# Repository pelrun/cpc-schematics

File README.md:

## Amstrad CPC6128 version 2 (MC0020x) schematic and pcb.

This is intended to be a reasonably accurate KiCad 6 transcription of the version 2 6128 pcb, with the 40010 Gate Array and the 24-pin disk data separator. The Amstrad service manuals don't bother to document this version, instead providing a mishmash of earlier and later revision schematics and pcb track layouts.

There are some liberties taken due to practical difficulties in reading the top layer of the PCB, so here's the priorities of this version:

- Schematic should match as closely as possible to the real board.
- All parts and part references and logical connectivity should match exactly.
- Part and via placement should match as closely as possible.
- Track routing should match closely on both sides of the pcb; all vias should be connected to the correct nets.
- Exact track poses may vary; original layout was done by hand and has varying angles; kicad layout is kept at 45 degrees.
- Track widths aren't correct everywhere; while the ground and power nets are handled by a netclass, a bunch of the tracks in the audio circuit need to have their widths manually adjusted.

Most part values should be correct, but I've not yet bothered to check any resistors - all values were copied from corresponding parts identified in the official schematics for the other revisions. Real values may be different, and additional resistors that are present but not documented elsewhere have been left with a value of "?".

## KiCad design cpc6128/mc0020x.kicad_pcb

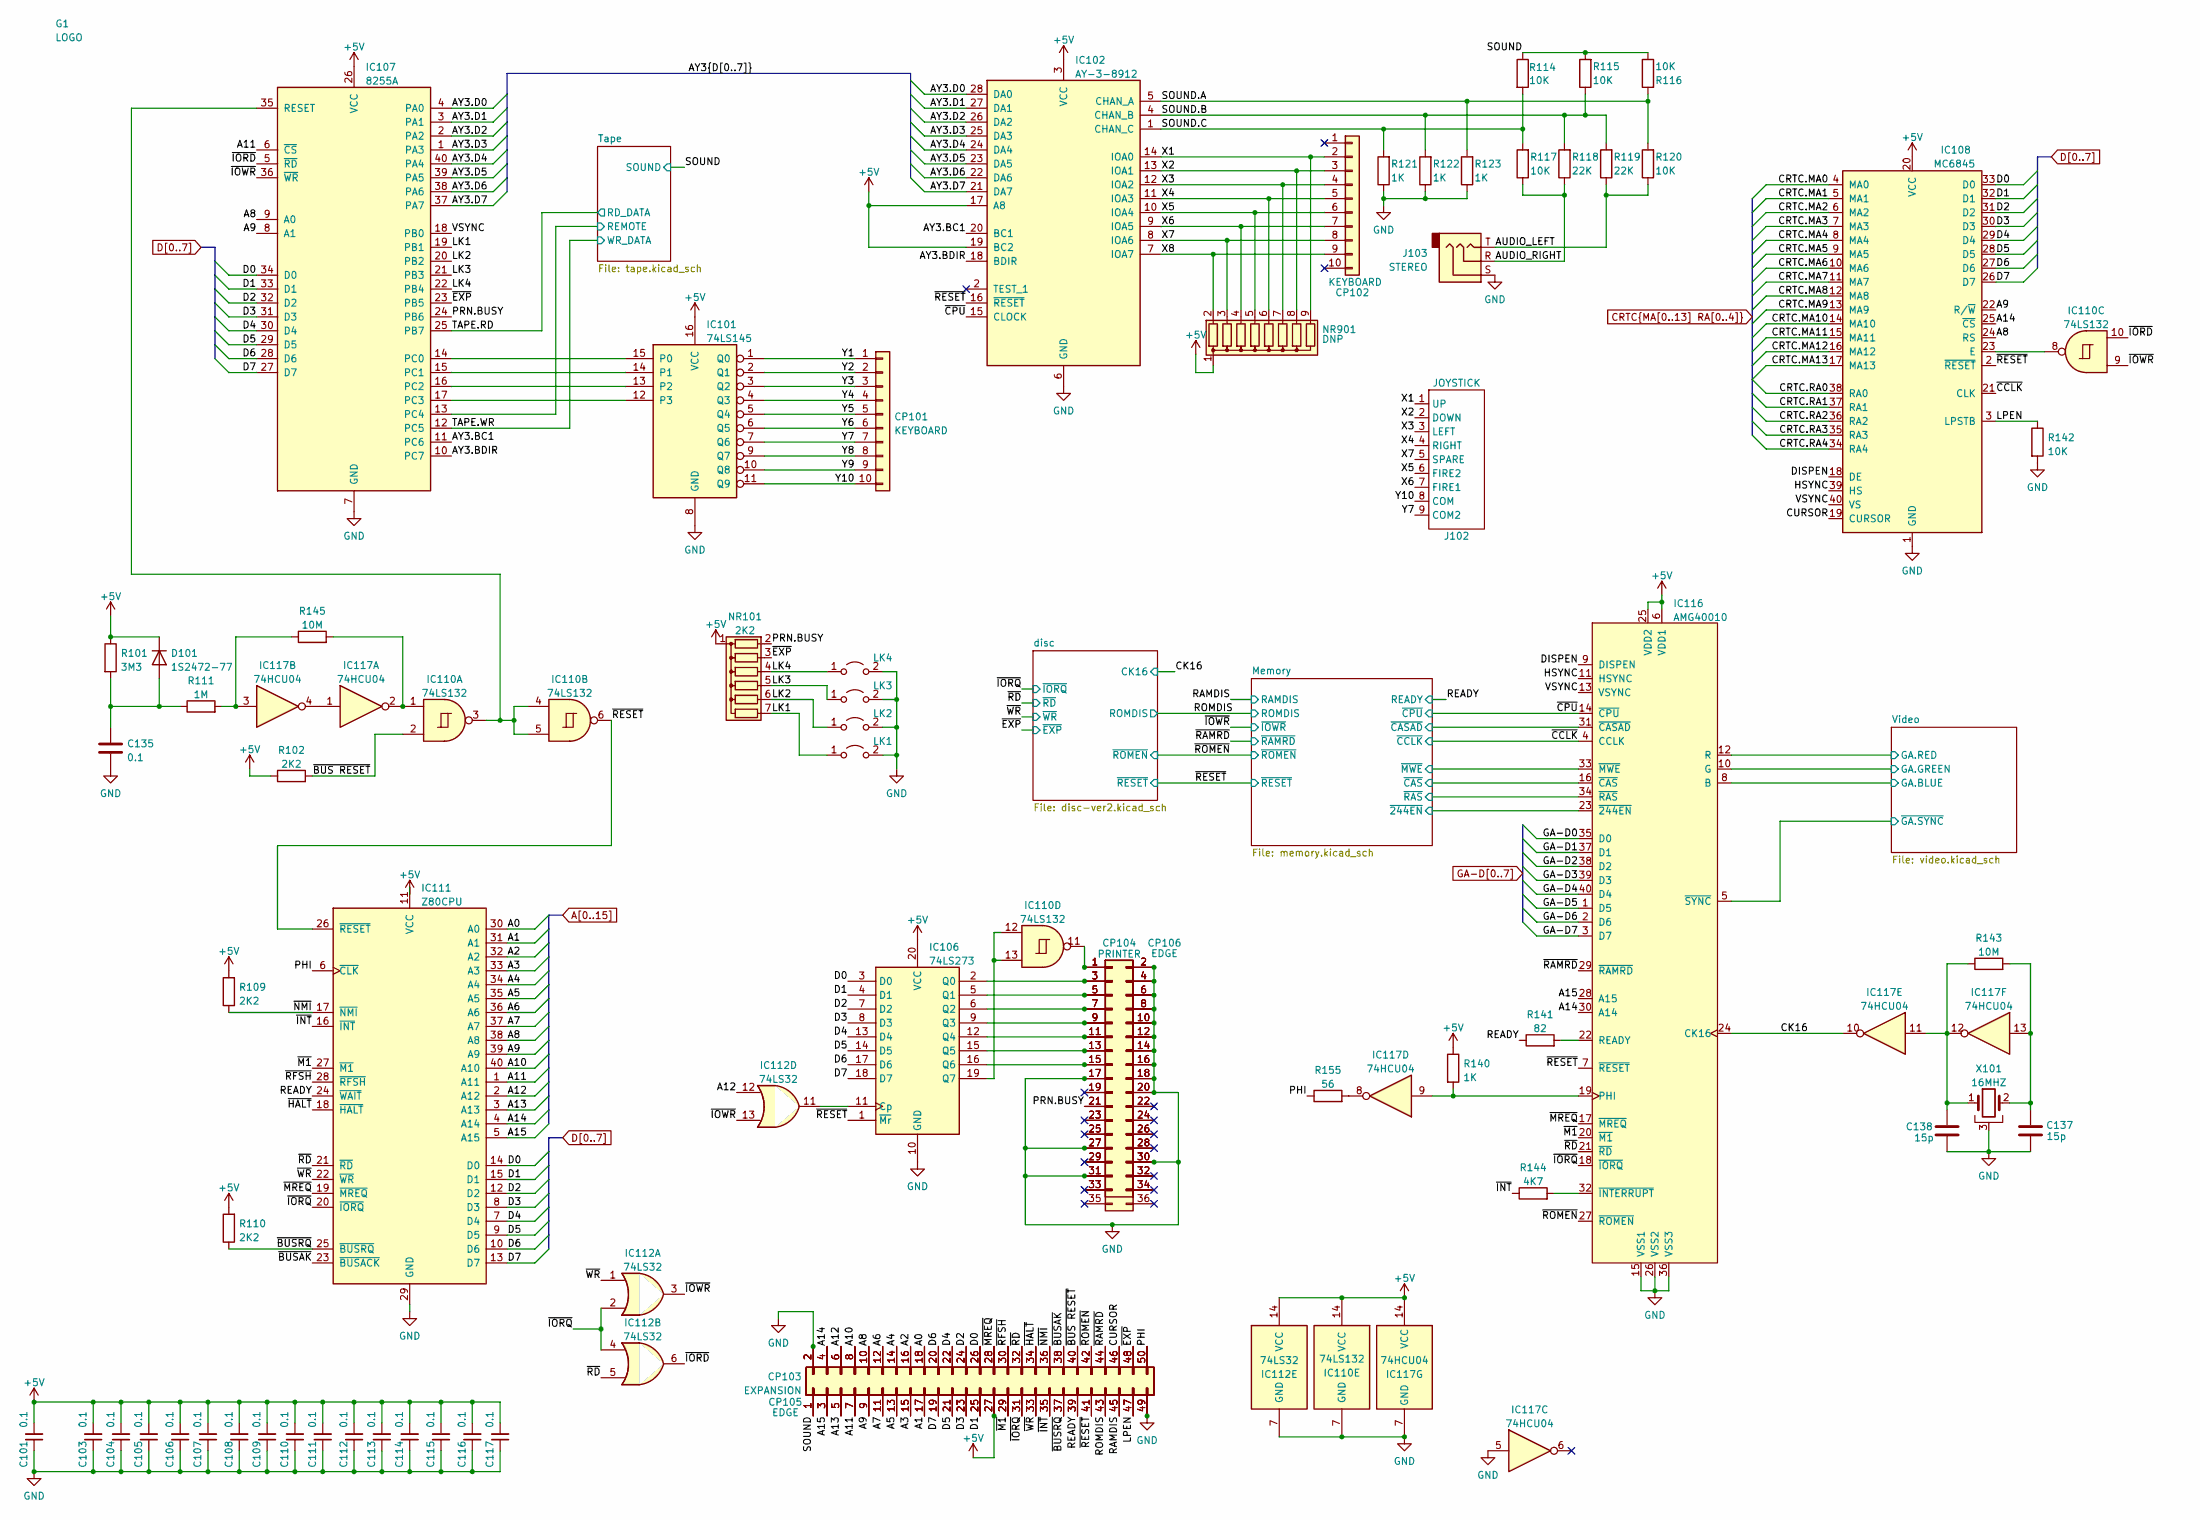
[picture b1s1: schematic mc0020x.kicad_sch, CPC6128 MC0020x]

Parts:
C101, C103, C104, C105, C106, C107, C108, C109, C110, C111, C112, C113, C114, C115, C116, C117, C135: 0.1; C_Disc_D4.3mm_W1.9mm_P5.00mm
C137, C138: 15p; C_Disc_D4.3mm_W1.9mm_P5.00mm
CP101, CP102: KEYBOARD; HBLB10S-5J
CP103: EXPANSION; 50-PIN-CENTRONICS
CP104: PRINTER; 36-PIN-CENTRONICS
CP105: EDGE; Edge_Conn_2x25
CP106: EDGE; Edge_Conn_2x17
D101: 1S2472-77; D_DO-35_SOD27_P10.16mm_Horizontal
G1: LOGO
IC101: 74LS145; DIP-16_W7.62mm
IC102: AY-3-8912; DIP-28_W15.24mm
IC106: 74LS273; DIP-20_W7.62mm
IC107: 8255A; DIP-40_W15.24mm
IC108: MC6845; DIP-40_W15.24mm
IC110: 74LS132; DIP-14_W7.62mm
IC111: Z80CPU; DIP-40_W15.24mm
IC112: 74LS32; DIP-14_W7.62mm
IC116: AMG40010; DIP-40_W15.24mm_Socket
IC117: 74HCU04; DIP-14_W7.62mm
J102: JOYSTICK; DSUB-9_Male_Horizontal_P2.77x2.54mm_EdgePinOffset9.40mm
J103: STEREO; HSJ1061-0104409
LK1, LK2, LK3, LK4: Jumper_2_Open; LINK
NR101: 2K2; R_Array_SIP7
NR901: DNP; R_Array_SIP9
R101: 3M3; R_Axial_DIN0207_L6.3mm_D2.5mm_P10.16mm_Horizontal
R102, R109, R110: 2K2; R_Axial_DIN0207_L6.3mm_D2.5mm_P10.16mm_Horizontal
R111: 1M; R_Axial_DIN0207_L6.3mm_D2.5mm_P10.16mm_Horizontal
R114, R115, R116, R117, R120, R142: 10K; R_Axial_DIN0207_L6.3mm_D2.5mm_P10.16mm_Horizontal
R118, R119: 22K; R_Axial_DIN0207_L6.3mm_D2.5mm_P10.16mm_Horizontal
R121, R122, R123, R140: 1K; R_Axial_DIN0207_L6.3mm_D2.5mm_P10.16mm_Horizontal
R141: 82; R_Axial_DIN0207_L6.3mm_D2.5mm_P10.16mm_Horizontal
R143, R145: 10M; R_Axial_DIN0207_L6.3mm_D2.5mm_P10.16mm_Horizontal
R144: 4K7; R_Axial_DIN0207_L6.3mm_D2.5mm_P10.16mm_Horizontal
R155: 56; R_Axial_DIN0207_L6.3mm_D2.5mm_P10.16mm_Horizontal
X101: 16MHZ; Crystal_HC18-U_Horizontal_1EP_style1

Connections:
+5V: C101.2, C103.2, C104.2, C105.2, C106.2, C107.2, C108.2, C109.2, C110.2, C111.2, C112.2, C113.2, C114.2, C115.2, C116.2, C117.2, CP103.27, CP105.27, D101.1 (K), IC101.16 (VCC), IC102.3 (VCC), IC102.17 (A8), IC102.19 (BC2), IC106.20 (VCC), IC107.26 (VCC), IC108.20 (VCC), IC110.14 (VCC), IC111.11 (VCC), IC112.14 (VCC), IC116.6 (VDD1), IC116.25 (VDD2), IC117.14 (VCC), NR101.1 (common), NR901.1 (common), R101.1, R102.1, R109.2, R110.2, R140.1; also elsewhere on the board
/AUDIO_LEFT: J103.T, R119.1, R120.1
/AUDIO_RIGHT: J103.R, R117.1, R118.1
/AY3.BC1: IC102.20 (BC1), IC107.11 (PC6)
/AY3.BDIR: IC102.18 (BDIR), IC107.10 (PC7)
/AY3.D0: IC102.28 (DA0), IC107.4 (PA0)
/AY3.D1: IC102.27 (DA1), IC107.3 (PA1)
/AY3.D2: IC102.26 (DA2), IC107.2 (PA2)
/AY3.D3: IC102.25 (DA3), IC107.1 (PA3)
/AY3.D4: IC102.24 (DA4), IC107.40 (PA4)
/AY3.D5: IC102.23 (DA5), IC107.39 (PA5)
/AY3.D6: IC102.22 (DA6), IC107.38 (PA6)
/AY3.D7: IC102.21 (DA7), IC107.37 (PA7)
/CK16: IC116.24 (CK16), IC117.10; also elsewhere on the board
/CURSOR: CP103.46, CP105.46, IC108.19 (CURSOR)
/DISPEN: IC108.18 (DE), IC116.9 (DISPEN)
/HSYNC: IC108.39 (HS), IC116.11 (HSYNC)
/LK1: IC107.19 (PB1), LK1.1 (A), NR101.7 (R6)
/LK2: IC107.20 (PB2), LK2.1 (A), NR101.6 (R5)
/LK3: IC107.21 (PB3), LK3.1 (A), NR101.5 (R4)
/LK4: IC107.22 (PB4), LK4.1 (A), NR101.4 (R3)
/LPEN: CP103.47, CP105.47, IC108.3 (LPSTB), R142.1
/Memory/~244EN: IC116.23 (~244EN); also elsewhere on the board
/Memory/~CASAD: IC116.31 (~CASAD); also elsewhere on the board
/Memory/~CAS: IC116.16 (~CAS); also elsewhere on the board
/Memory/~MWE: IC116.33 (~MWE); also elsewhere on the board
/Memory/~RAS: IC116.34 (~RAS); also elsewhere on the board
/PHI: CP103.50, CP105.50, IC111.6 (~CLK), R155.1
/PRN.BUSY: CP104.21, CP106.21, IC107.24 (PB6), NR101.2 (R1)
/RAMDIS: CP103.45, CP105.45; also elsewhere on the board
/READY: CP103.39, CP105.39, IC111.24 (~WAIT), R141.1; also elsewhere on the board
/ROMDIS: CP103.43, CP105.43; also elsewhere on the board
/SOUND: CP103.1, CP105.1, R114.1, R115.2, R116.1; also elsewhere on the board
/SOUND.A: IC102.5 (CHAN_A), R116.2, R120.2, R123.2
/SOUND.B: IC102.4 (CHAN_B), R115.1, R118.2, R119.2, R122.2
/SOUND.C: IC102.1 (CHAN_C), R114.2, R117.2, R121.2
/TAPE.RD: IC107.25 (PB7); also elsewhere on the board
/TAPE.WR: IC107.12 (PC5); also elsewhere on the board
/Tape/REMOTE: IC107.13 (PC4); also elsewhere on the board
/VSYNC: IC107.18 (PB0), IC108.40 (VS), IC116.13 (VSYNC)
/Video/GA.BLUE: IC116.8 (B); also elsewhere on the board
/Video/GA.GREEN: IC116.10 (G); also elsewhere on the board
/Video/GA.RED: IC116.12 (R); also elsewhere on the board
/Video/~GA.SYNC: IC116.5 (~SYNC); also elsewhere on the board
/X1: CP102.2, IC102.14 (IOA0), J102.1 (UP), NR901.9 (R8)
/X2: CP102.3, IC102.13 (IOA1), J102.2 (DOWN), NR901.8 (R7)
/X3: CP102.4, IC102.12 (IOA2), J102.3 (LEFT), NR901.7 (R6)
/X4: CP102.5, IC102.11 (IOA3), J102.4 (RIGHT), NR901.6 (R5)
/X5: CP102.6, IC102.10 (IOA4), J102.6 (FIRE2), NR901.5 (R4)
/X6: CP102.7, IC102.9 (IOA5), J102.7 (FIRE1), NR901.4 (R3)
/X7: CP102.8, IC102.8 (IOA6), J102.5 (SPARE), NR901.3 (R2)
/X8: CP102.9, IC102.7 (IOA7), NR901.2 (R1)
/Y1: CP101.1, IC101.1 (Q0)
/Y2: CP101.2, IC101.2 (Q1)
/Y3: CP101.3, IC101.3 (Q2)
/Y4: CP101.4, IC101.4 (Q3)
/Y5: CP101.5, IC101.5 (Q4)
/Y6: CP101.6, IC101.6 (Q5)
/Y7: CP101.7, IC101.7 (Q6), J102.9 (COM2)
/Y8: CP101.8, IC101.9 (Q7)
/Y9: CP101.9, IC101.10 (Q8)
/Y10: CP101.10, IC101.11 (Q9), J102.8 (COM)
/~BUS RESET: CP103.40, CP105.40, IC110.2, R102.2
/~BUSAK: CP103.38, CP105.38, IC111.23 (~BUSACK)
/~BUSRQ: CP103.37, CP105.37, IC111.25 (~BUSRQ), R110.1
/~CCLK: IC108.21 (CLK), IC116.4 (CCLK); also elsewhere on the board
/~CPU: IC102.15 (CLOCK), IC116.14 (~CPU); also elsewhere on the board
/~EXP: CP103.48, CP105.48, IC107.23 (PB5), NR101.3 (R2); also elsewhere on the board
/~HALT: CP103.34, CP105.34, IC111.18 (~HALT)
/~INT: CP103.35, CP105.35, IC111.16 (~INT), R144.1
/~IORD: IC107.5 (~RD), IC110.10, IC112.6
/~IORQ: CP103.31, CP105.31, IC111.20 (~IORQ), IC112.2, IC112.4, IC116.18 (~IORQ); also elsewhere on the board
/~IOWR: IC107.36 (~WR), IC110.9, IC112.3, IC112.13; also elsewhere on the board
/~M1: CP103.29, CP105.29, IC111.27 (~M1), IC116.20 (~M1)
/~MREQ: CP103.28, CP105.28, IC111.19 (~MREQ), IC116.17 (~MREQ)
/~NMI: CP103.36, CP105.36, IC111.17 (~NMI), R109.1
/~RAMRD: CP103.44, CP105.44, IC116.29 (~RAMRD); also elsewhere on the board
/~RD: CP103.32, CP105.32, IC111.21 (~RD), IC112.5, IC116.21 (~RD); also elsewhere on the board
/~RESET: CP103.41, CP105.41, IC102.16 (~RESET), IC106.1 (~Mr), IC108.2 (~RESET), IC110.6, IC111.26 (~RESET), IC116.7 (~RESET); also elsewhere on the board
/~RFSH: CP103.30, CP105.30, IC111.28 (~RFSH)
/~ROMEN: CP103.42, CP105.42, IC116.27 (~ROMEN); also elsewhere on the board
/~WR: CP103.33, CP105.33, IC111.22 (~WR), IC112.1; also elsewhere on the board
A0: CP103.18, CP105.18, IC111.30 (A0); also elsewhere on the board
A1: CP103.17, CP105.17, IC111.31 (A1); also elsewhere on the board
A2: CP103.16, CP105.16, IC111.32 (A2); also elsewhere on the board
A3: CP103.15, CP105.15, IC111.33 (A3); also elsewhere on the board
A4: CP103.14, CP105.14, IC111.34 (A4); also elsewhere on the board
A5: CP103.13, CP105.13, IC111.35 (A5); also elsewhere on the board
A6: CP103.12, CP105.12, IC111.36 (A6); also elsewhere on the board
A7: CP103.11, CP105.11, IC111.37 (A7); also elsewhere on the board
A8: CP103.10, CP105.10, IC107.9 (A0), IC108.24 (RS), IC111.38 (A8); also elsewhere on the board
A9: CP103.9, CP105.9, IC107.8 (A1), IC108.22 (R/~W), IC111.39 (A9); also elsewhere on the board
A10: CP103.8, CP105.8, IC111.40 (A10); also elsewhere on the board
A11: CP103.7, CP105.7, IC107.6 (~CS), IC111.1 (A11); also elsewhere on the board
A12: CP103.6, CP105.6, IC111.2 (A12), IC112.12; also elsewhere on the board
A13: CP103.5, CP105.5, IC111.3 (A13); also elsewhere on the board
A14: CP103.4, CP105.4, IC108.25 (~CS), IC111.4 (A14), IC116.30 (A14); also elsewhere on the board
A15: CP103.3, CP105.3, IC111.5 (A15), IC116.28 (A15); also elsewhere on the board
CRTC.MA0: IC108.4 (MA0); also elsewhere on the board
CRTC.MA1: IC108.5 (MA1); also elsewhere on the board
CRTC.MA2: IC108.6 (MA2); also elsewhere on the board
CRTC.MA3: IC108.7 (MA3); also elsewhere on the board
CRTC.MA4: IC108.8 (MA4); also elsewhere on the board
CRTC.MA5: IC108.9 (MA5); also elsewhere on the board
CRTC.MA6: IC108.10 (MA6); also elsewhere on the board
CRTC.MA7: IC108.11 (MA7); also elsewhere on the board
CRTC.MA8: IC108.12 (MA8); also elsewhere on the board
CRTC.MA9: IC108.13 (MA9); also elsewhere on the board
CRTC.MA10: IC108.14 (MA10)
CRTC.MA11: IC108.15 (MA11)
CRTC.MA12: IC108.16 (MA12); also elsewhere on the board
CRTC.MA13: IC108.17 (MA13); also elsewhere on the board
CRTC.RA0: IC108.38 (RA0); also elsewhere on the board
CRTC.RA1: IC108.37 (RA1); also elsewhere on the board
CRTC.RA2: IC108.36 (RA2); also elsewhere on the board
CRTC.RA3: IC108.35 (RA3)
CRTC.RA4: IC108.34 (RA4)
D0: CP103.26, CP105.26, IC106.3 (D0), IC107.34 (D0), IC108.33 (D0), IC111.14 (D0); also elsewhere on the board
D1: CP103.25, CP105.25, IC106.4 (D1), IC107.33 (D1), IC108.32 (D1), IC111.15 (D1); also elsewhere on the board
D2: CP103.24, CP105.24, IC106.7 (D2), IC107.32 (D2), IC108.31 (D2), IC111.12 (D2); also elsewhere on the board
D3: CP103.23, CP105.23, IC106.8 (D3), IC107.31 (D3), IC108.30 (D3), IC111.8 (D3); also elsewhere on the board
D4: CP103.22, CP105.22, IC106.13 (D4), IC107.30 (D4), IC108.29 (D4), IC111.7 (D4); also elsewhere on the board
D5: CP103.21, CP105.21, IC106.14 (D5), IC107.29 (D5), IC108.28 (D5), IC111.9 (D5); also elsewhere on the board
D6: CP103.20, CP105.20, IC106.17 (D6), IC107.28 (D6), IC108.27 (D6), IC111.10 (D6); also elsewhere on the board
D7: CP103.19, CP105.19, IC106.18 (D7), IC107.27 (D7), IC108.26 (D7), IC111.13 (D7); also elsewhere on the board
GA-D0: IC116.35 (D0); also elsewhere on the board
GA-D1: IC116.37 (D1); also elsewhere on the board
GA-D2: IC116.38 (D2); also elsewhere on the board
GA-D3: IC116.39 (D3); also elsewhere on the board
GA-D4: IC116.40 (D4); also elsewhere on the board
GA-D5: IC116.1 (D5); also elsewhere on the board
GA-D6: IC116.2 (D6); also elsewhere on the board
GA-D7: IC116.3 (D7); also elsewhere on the board
GND: C101.1, C103.1, C104.1, C105.1, C106.1, C107.1, C108.1, C109.1, C110.1, C111.1, C112.1, C113.1, C114.1, C115.1, C116.1, C117.1, C135.2, C137.1, C138.2, CP103.2, CP103.49, CP104.2, CP104.4, CP104.6, CP104.8, CP104.10, CP104.12, CP104.14, CP104.16, CP104.17, CP104.18, CP104.20, CP104.27, CP104.30, CP104.31, CP105.2, CP105.49, CP106.2, CP106.4, CP106.6, CP106.8, CP106.10, CP106.12, CP106.14, CP106.16, CP106.17, CP106.18, CP106.20, CP106.27, CP106.30, CP106.31, IC101.8 (GND), IC102.6 (GND), IC106.10 (GND), IC107.7 (GND), IC108.1 (GND), IC110.7 (GND), IC111.29 (GND), IC112.7 (GND), IC116.15 (VSS1), IC116.26 (VSS2), IC116.36 (VSS3), IC117.5, IC117.7 (GND), J103.S, LK1.2 (B), LK2.2 (B), LK3.2 (B), LK4.2 (B), R121.1, R122.1, R123.1, R142.2, X101.3; also elsewhere on the board
unnamed: C137.2, IC117.13, R143.2, X101.2
unnamed: C138.1, IC117.11, IC117.12, R143.1, X101.1
unnamed: CP104.1, CP106.1, IC110.11
unnamed: CP104.3, CP106.3, IC106.2 (Q0)
unnamed: CP104.5, CP106.5, IC106.5 (Q1)
unnamed: CP104.7, CP106.7, IC106.6 (Q2)
unnamed: CP104.9, CP106.9, IC106.9 (Q3)
unnamed: CP104.11, CP106.11, IC106.12 (Q4)
unnamed: CP104.13, CP106.13, IC106.15 (Q5)
unnamed: CP104.15, CP106.15, IC106.16 (Q6)
unnamed: C135.1, D101.2 (A), R101.2, R111.1
unnamed: IC101.15 (P0), IC107.14 (PC0)
unnamed: IC101.14 (P1), IC107.15 (PC1)
unnamed: IC101.13 (P2), IC107.16 (PC2)
unnamed: IC101.12 (P3), IC107.17 (PC3)
unnamed: IC106.11 (Cp), IC112.11
unnamed: IC106.19 (Q7), IC110.12, IC110.13
unnamed: IC107.35 (RESET), IC110.3, IC110.4, IC110.5
unnamed: IC108.23 (E), IC110.8
unnamed: IC110.1, IC117.2, R145.2
unnamed: IC116.19 (PHI), IC117.9, R140.2
unnamed: IC116.22 (READY), R141.2
unnamed: IC116.32 (~INTERRUPT), R144.2
unnamed: IC117.1, IC117.4
unnamed: IC117.3, R111.2, R145.1
unnamed: IC117.8, R155.2

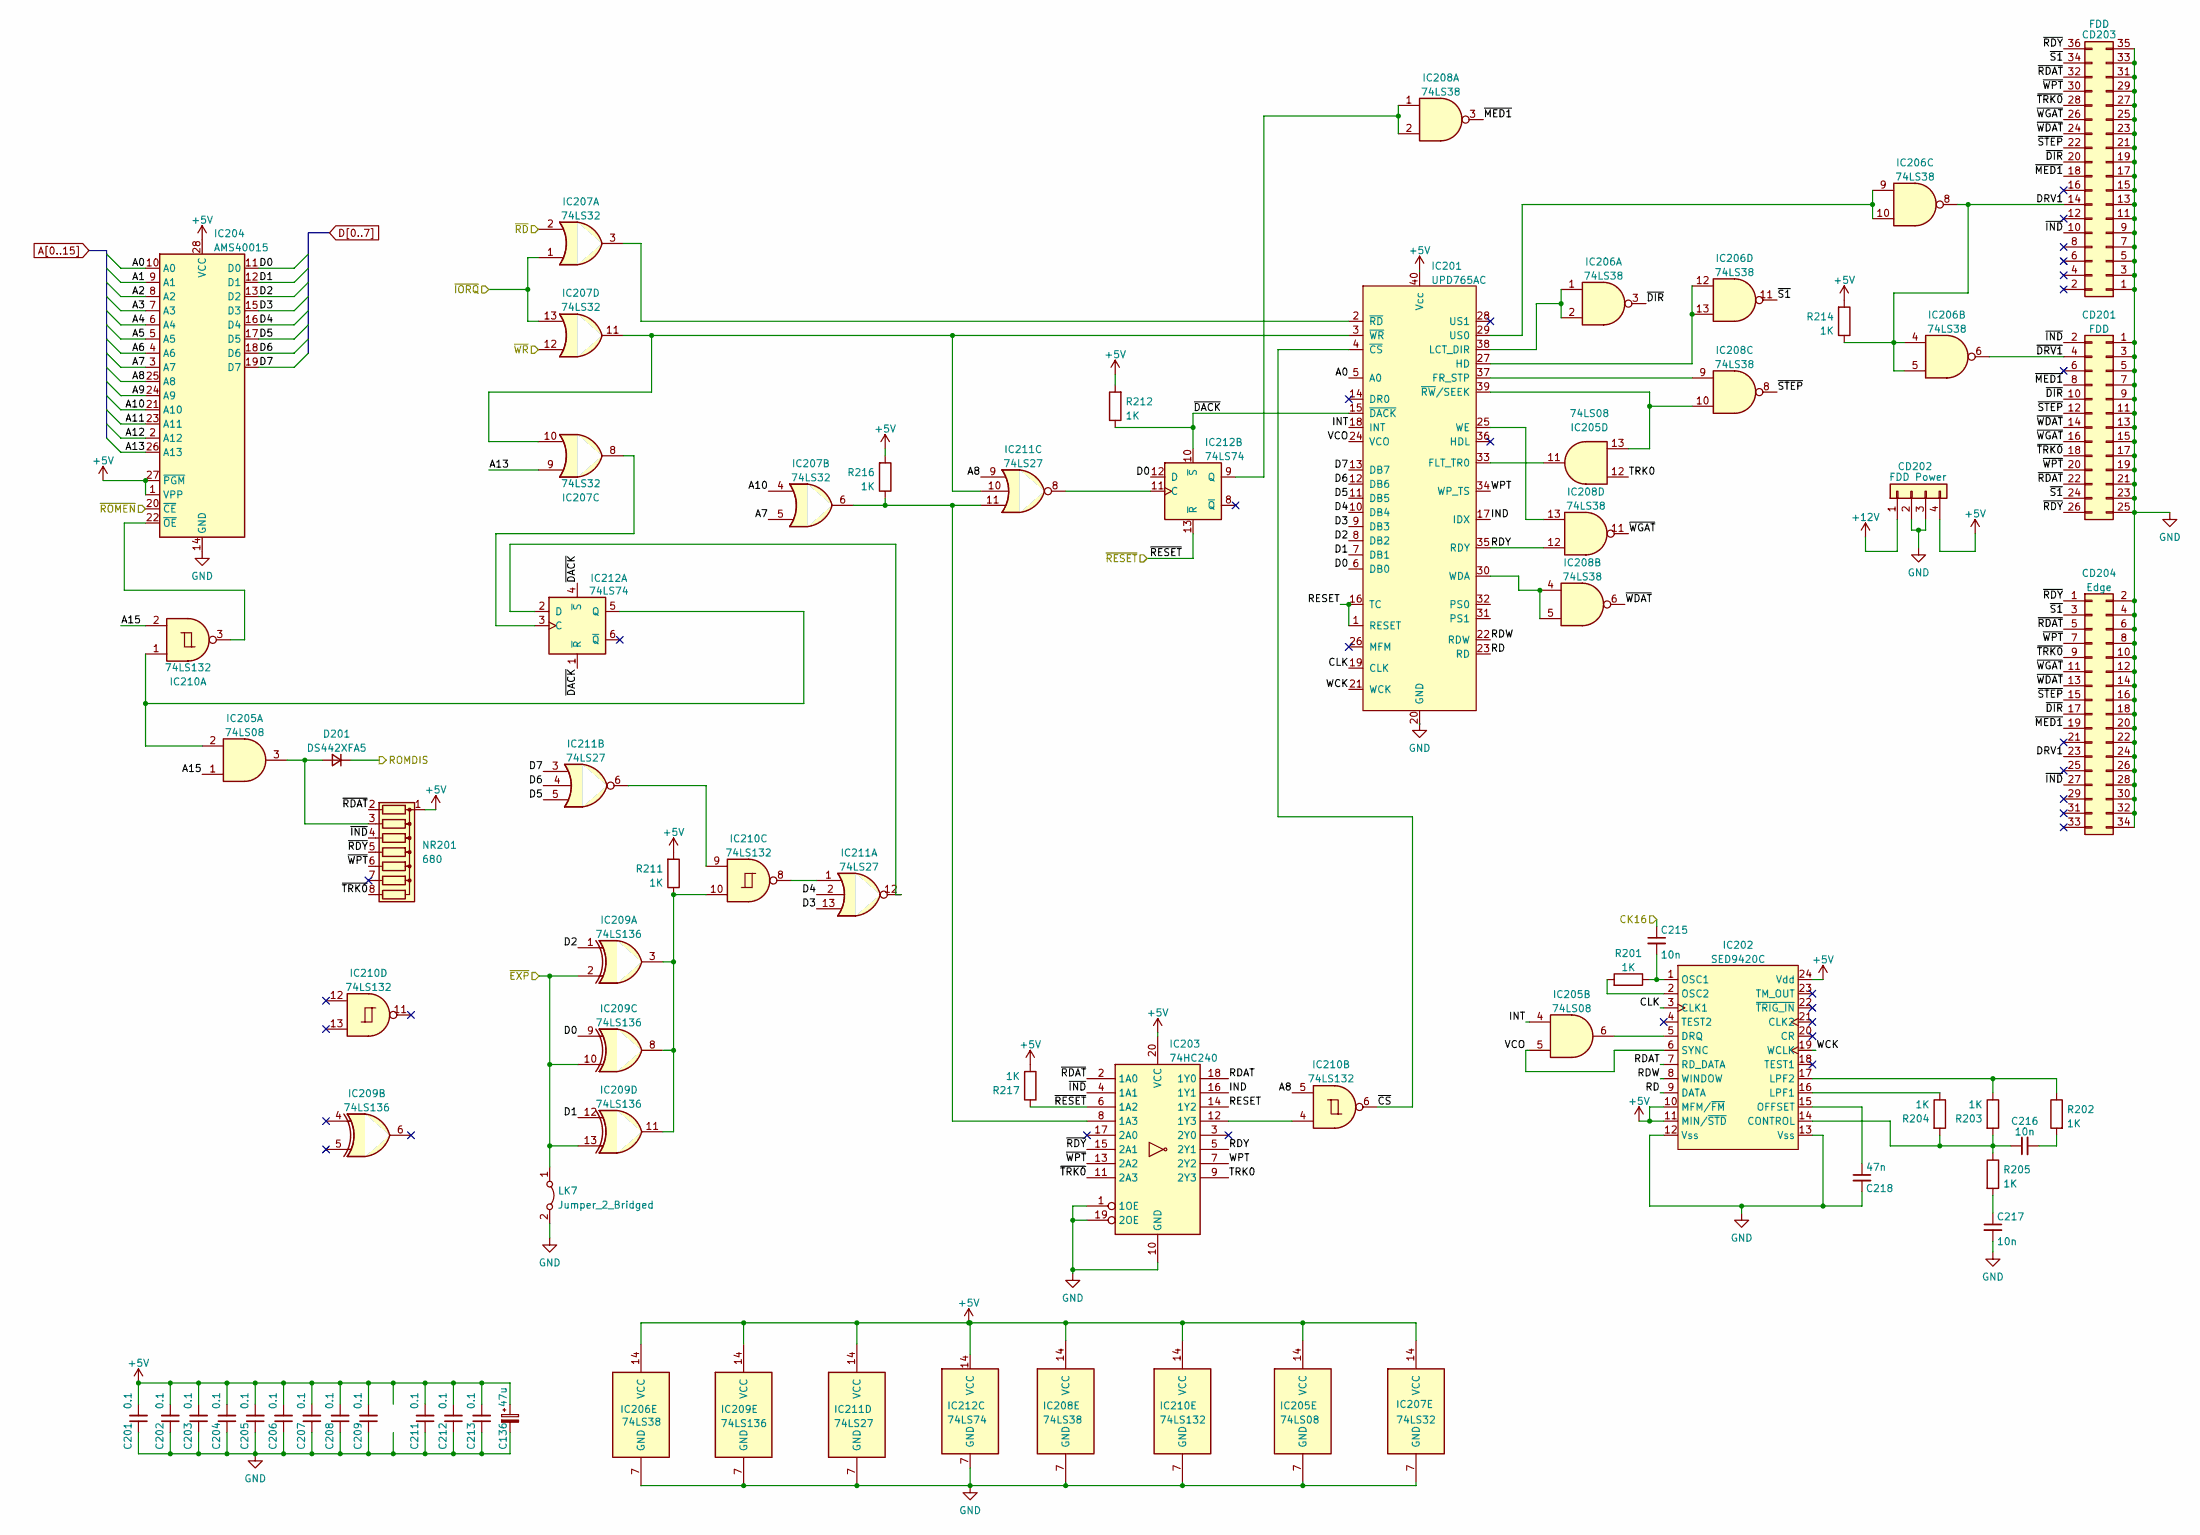
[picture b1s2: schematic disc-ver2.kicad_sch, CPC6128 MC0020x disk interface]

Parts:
C136: 47u; CP_Radial_D4.0mm_P5.00mm
C201, C202, C203, C204, C205, C206, C207, C208, C209, C211, C212, C213: 0.1; C_Disc_D4.3mm_W1.9mm_P5.00mm
C215, C216, C217: 10n; C_Rect_L7.0mm_W2.0mm_P5.00mm
C218: 47n; C_Rect_L7.0mm_W2.0mm_P5.00mm
CD201: FDD; IDC-Header_2x13_P2.54mm_Vertical
CD202: FDD Power; FDD_Power
CD203: FDD; 36-PIN-CENTRONICS
CD204: Edge; Edge_Conn_2x17
D201: DS442XFA5; D_DO-35_SOD27_P10.16mm_Horizontal
IC201: UPD765AC; DIP-40_W15.24mm
IC202: SED9420C; DIP-24_W15.24mm
IC203: 74HC240; DIP-20_W7.62mm
IC204: AMS40015; DIP-28_W15.24mm
IC205: 74LS08; DIP-14_W7.62mm
IC206, IC208: 74LS38; DIP-14_W7.62mm
IC207: 74LS32; DIP-14_W7.62mm
IC209: 74LS136; DIP-14_W7.62mm
IC210: 74LS132; DIP-14_W7.62mm
IC211: 74LS27; DIP-14_W7.62mm
IC212: 74LS74; DIP-14_W7.62mm
LK7: Jumper_2_Bridged; LINK
NR201: 680; R_Array_SIP8
R201, R202, R203, R204, R205, R211, R212, R214, R216, R217: 1K; R_Axial_DIN0207_L6.3mm_D2.5mm_P10.16mm_Horizontal

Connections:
+5V: C136.1, C201.2, C202.2, C203.2, C204.2, C205.2, C206.2, C207.2, C208.2, C209.2, C211.2, C212.2, C213.2, CD202.4, IC201.40 (Vcc), IC202.10 (MFM/~FM), IC202.11 (MIN/~STD), IC202.24 (Vdd), IC203.20 (VCC), IC204.1 (VPP), IC204.27 (~PGM), IC204.28 (VCC), IC205.14 (VCC), IC206.14 (VCC), IC207.14 (VCC), IC208.14 (VCC), IC209.14 (VCC), IC210.14 (VCC), IC211.14 (VCC), IC212.14 (VCC), NR201.1 (common), R211.2, R212.2, R214.2, R216.2, R217.2; also elsewhere on the board
+12V: CD202.1; also elsewhere on the board
/CK16: C215.1; also elsewhere on the board
/ROMDIS: D201.1 (K); also elsewhere on the board
/disc/CLK: IC201.19 (CLK), IC202.3 (CLK1)
/disc/DRV1: CD203.14, CD204.23, IC206.4, IC206.5, IC206.8, R214.1
/disc/IND: IC201.17 (IDX), IC203.16 (1Y1)
/disc/INT: IC201.18 (INT), IC205.4
/disc/RD: IC201.23 (RD), IC202.9 (DATA)
/disc/RDAT: IC202.7 (RD_DATA), IC203.18 (1Y0)
/disc/RDW: IC201.22 (RDW), IC202.8 (WINDOW)
/disc/RDY: IC201.35 (RDY), IC203.5 (2Y1), IC208.12
/disc/RESET: IC201.1 (RESET), IC201.16 (TC), IC203.14 (1Y2)
/disc/TRK0: IC203.9 (2Y3), IC205.12
/disc/VCO: IC201.24 (VCO), IC202.6 (SYNC), IC205.5
/disc/WCK: IC201.21 (WCK), IC202.19 (WCLK)
/disc/WPT: IC201.34 (WP_TS), IC203.7 (2Y2)
/disc/~CS: IC201.4 (~CS), IC210.6
/disc/~DACK: IC201.15 (~DACK), IC212.1 (~R), IC212.4 (~S), IC212.10 (~S), R212.1
/disc/~DIR: CD201.10, CD203.20, CD204.17, IC206.3
/disc/~DRV1: CD201.4, IC206.6
/disc/~IND: CD201.2, CD203.10, CD204.27, IC203.4 (1A1), NR201.4 (R3)
/disc/~MED1: CD201.8, CD203.18, CD204.19, IC208.3
/disc/~RDAT: CD201.22, CD203.32, CD204.5, IC203.2 (1A0), NR201.2 (R1)
/disc/~RDY: CD201.26, CD203.36, CD204.1, IC203.15 (2A1), NR201.5 (R4)
/disc/~S1: CD201.24, CD203.34, CD204.3, IC206.11
/disc/~STEP: CD201.12, CD203.22, CD204.15, IC208.8
/disc/~TRK0: CD201.18, CD203.28, CD204.9, IC203.11 (2A3), NR201.8 (R7)
/disc/~WDAT: CD201.14, CD203.24, CD204.13, IC208.6
/disc/~WGAT: CD201.16, CD203.26, CD204.11, IC208.11
/disc/~WPT: CD201.20, CD203.30, CD204.7, IC203.13 (2A2), NR201.6 (R5)
/~EXP: IC209.2, IC209.10, IC209.13, LK7.1 (A); also elsewhere on the board
/~IORQ: IC207.1, IC207.13; also elsewhere on the board
/~RD: IC207.2; also elsewhere on the board
/~RESET: IC203.6 (1A2), IC212.13 (~R), R217.1; also elsewhere on the board
/~ROMEN: IC204.20 (~CE); also elsewhere on the board
/~WR: IC207.12; also elsewhere on the board
A0: IC201.5 (A0), IC204.10 (A0); also elsewhere on the board
A1: IC204.9 (A1); also elsewhere on the board
A2: IC204.8 (A2); also elsewhere on the board
A3: IC204.7 (A3); also elsewhere on the board
A4: IC204.6 (A4); also elsewhere on the board
A5: IC204.5 (A5); also elsewhere on the board
A6: IC204.4 (A6); also elsewhere on the board
A7: IC204.3 (A7), IC207.5; also elsewhere on the board
A8: IC204.25 (A8), IC210.5, IC211.9; also elsewhere on the board
A9: IC204.24 (A9); also elsewhere on the board
A10: IC204.21 (A10), IC207.4; also elsewhere on the board
A11: IC204.23 (A11); also elsewhere on the board
A12: IC204.2 (A12); also elsewhere on the board
A13: IC204.26 (A13), IC207.9; also elsewhere on the board
A15: IC205.1, IC210.2; also elsewhere on the board
D0: IC201.6 (DB0), IC204.11 (D0), IC209.9, IC212.12 (D); also elsewhere on the board
D1: IC201.7 (DB1), IC204.12 (D1), IC209.12; also elsewhere on the board
D2: IC201.8 (DB2), IC204.13 (D2), IC209.1; also elsewhere on the board
D3: IC201.9 (DB3), IC204.15 (D3), IC211.13; also elsewhere on the board
D4: IC201.10 (DB4), IC204.16 (D4), IC211.2; also elsewhere on the board
D5: IC201.11 (DB5), IC204.17 (D5), IC211.5; also elsewhere on the board
D6: IC201.12 (DB6), IC204.18 (D6), IC211.4; also elsewhere on the board
D7: IC201.13 (DB7), IC204.19 (D7), IC211.3; also elsewhere on the board
GND: C136.2, C201.1, C202.1, C203.1, C204.1, C205.1, C206.1, C207.1, C208.1, C209.1, C211.1, C212.1, C213.1, C217.2, C218.2, CD201.1, CD201.3, CD201.5, CD201.7, CD201.9, CD201.11, CD201.13, CD201.15, CD201.17, CD201.19, CD201.21, CD201.23, CD201.25, CD202.2, CD202.3, CD203.1, CD203.3, CD203.5, CD203.7, CD203.9, CD203.11, CD203.13, CD203.15, CD203.17, CD203.19, CD203.21, CD203.23, CD203.25, CD203.27, CD203.29, CD203.31, CD203.33, CD203.35, CD204.2, CD204.4, CD204.6, CD204.8, CD204.10, CD204.12, CD204.14, CD204.16, CD204.18, CD204.20, CD204.22, CD204.24, CD204.26, CD204.28, CD204.30, CD204.32, CD204.34, IC201.20 (GND), IC202.12 (Vss), IC202.13 (Vss), IC203.1 (1OE), IC203.10 (GND), IC203.19 (2OE), IC204.14 (GND), IC205.7 (GND), IC206.7 (GND), IC207.7 (GND), IC208.7 (GND), IC209.7 (GND), IC210.7 (GND), IC211.7 (GND), IC212.7 (GND), LK7.2 (B); also elsewhere on the board
unnamed: C216.2, R202.2
unnamed: C217.1, R205.2
unnamed: D201.2 (A), IC205.3, NR201.3 (R2)
unnamed: IC201.33 (FLT_TR0), IC205.11
unnamed: IC201.37 (FR_STP), IC208.9
unnamed: IC201.27 (HD), IC206.12, IC206.13
unnamed: IC201.38 (LCT_DIR), IC206.1, IC206.2
unnamed: IC201.29 (US0), IC206.9, IC206.10
unnamed: IC201.30 (WDA), IC208.4, IC208.5
unnamed: IC201.25 (WE), IC208.13
unnamed: IC201.2 (~RD), IC207.3
unnamed: IC201.39 (~RW/SEEK), IC205.13, IC208.10
unnamed: IC201.3 (~WR), IC207.10, IC207.11, IC211.10
unnamed: C216.1, IC202.14 (CONTROL), R203.2, R204.2, R205.1
unnamed: IC202.5 (DRQ), IC205.6
unnamed: IC202.16 (LPF1), R204.1
unnamed: IC202.17 (LPF2), R202.1, R203.1
unnamed: C218.1, IC202.15 (OFFSET)
unnamed: C215.2, IC202.1 (OSC1), R201.1
unnamed: IC202.2 (OSC2), R201.2
unnamed: IC203.8 (1A3), IC207.6, IC211.11, R216.1
unnamed: IC203.12 (1Y3), IC210.4
unnamed: IC204.22 (~OE), IC210.3
unnamed: IC209.3, IC209.8, IC209.11, IC210.10, R211.1
unnamed: IC210.8, IC211.1
unnamed: IC210.9, IC211.6
unnamed: IC207.8, IC212.3 (C)
unnamed: IC211.12, IC212.2 (D)
unnamed: IC205.2, IC210.1, IC212.5 (Q)
unnamed: IC211.8, IC212.11 (C)
unnamed: IC208.1, IC208.2, IC212.9 (Q)
